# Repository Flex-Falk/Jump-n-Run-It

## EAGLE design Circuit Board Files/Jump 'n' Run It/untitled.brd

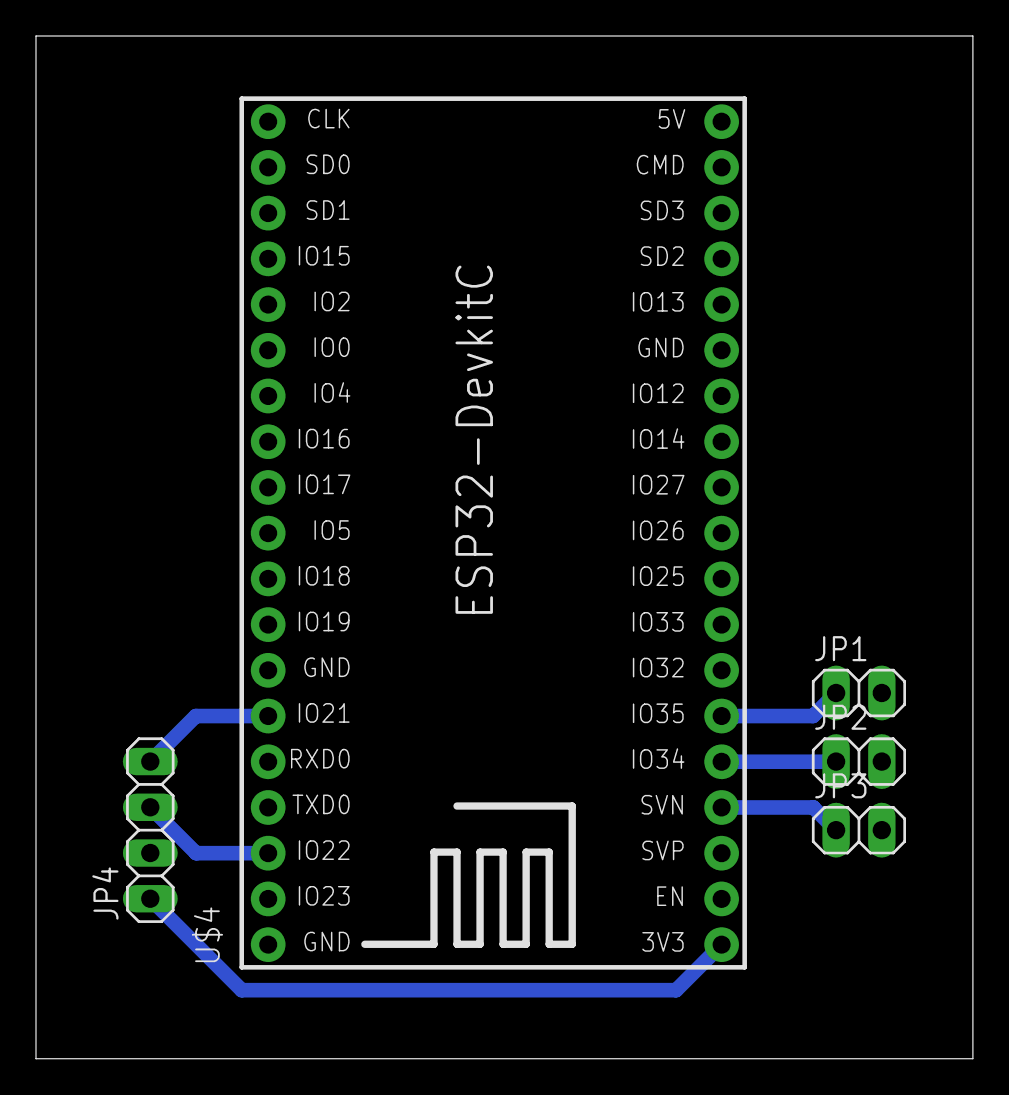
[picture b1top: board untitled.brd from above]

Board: 2 copper layers, 52.0 x 56.8 mm, 5 parts (0 on the bottom side), 7 nets.

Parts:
JP1, JP2, JP3: 1X02
JP4: 1X04
U$4: ESP32DEVKITC; ESP32-DEVKITC

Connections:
GND: JP1.2, JP2.2, JP3.2, JP4.2, U$4.38
unnamed: JP1.1, U$4.6
unnamed: JP2.1, U$4.5
unnamed: JP3.1, U$4.4
unnamed: JP4.1, U$4.1
unnamed: JP4.4, U$4.33
unnamed: JP4.3, U$4.36

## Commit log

2024-04-05 Added Hand-Drawn Sketch
    Variante Matte
2024-04-11 Basic Architecture, Organized Planning stuff
2024-04-11 Correction
2024-04-18 Created Test-Code for the Capacitive Pressure Sensor
2024-04-25 Functioning RunningMat code
2024-04-25 Small Corrections for ESP code
2024-04-26 Added Endless Game Prototype
    Mein bisheriger Fortschritt mit dem Unity Game, habe noch ein paar Fehler aus dem Tutorial fixen können. Hoffe es ist nicht zu groß für GitHub ^^
2024-04-29 Emulate Key input through ESP
2024-04-30 Updated Architecture
2024-05-01 Added Screenshots of Game
2024-05-02 gitignore
2024-05-02 gitIgnore Update
2024-05-02 Input Handler
2024-05-02 Update gitignore
2024-05-02 RunningMat should now correctly identify steps
2024-05-02 Coherent naming convention (instead of "mat" we use "board")
2024-05-02 Improve documentation for the ESP32 code
2024-05-08 Added Prefabs
    Die Straße generiert sich nun zufällig für ein unendliches Level und es gibt einen GameOver Screen wenn der Spieler mit einem Hindernis collided
2024-05-08 Added Screenshots
2024-05-09 Input + Controll Update
    big changes to the way the player is controlled and moving
2024-05-11 Include EventDataHook, UI to set port, baudrate
2024-05-16 Fixed and Tweaked code for the actual running boards
2024-05-20 Added Crouching + Screenshots
    Man kann nun im Game Mode über die Tastatur mit "c" den Player crouchen damit er unter den größeren Barrieren hindurch kann.
2024-05-27 Added Player Asset + Animations
2024-05-28 Circuit Board Files
2024-05-29 GyrosensorCase Model
2024-05-30 Animation base fix: stuff didnt got pushed properly last time
2024-05-31 Fixed Animations for Jumping & Crouching
2024-06-01 add mpu model
2024-06-01 Add server to use Bluetooth with unity via IPCs
    remove gravity from IMU
    TODO: write handle to communicate the server with unity
2024-06-02 Inital Port is set correctly at startup
2024-06-02 Disable controls when Game Over
2024-06-02 Added SFX and music and fixed unnecessary port display
2024-06-02 Quieter music
2024-06-02 JumpInput Fix
2024-06-02 Crouch Fix & Audio Tweak
2024-06-02 Added Grass, Walls and Lighting
2024-06-02 Models of all the Parts
2024-06-03 Added Coins to collect
2024-06-03 Revert "Added Coins to collect"
    This reverts commit 750d32fb50990cda842bd36838d8ff7ba60380a6.
2024-06-03 Added Screenshot
2024-06-03 Added PowerUps
    Can be collected but have no function yet
2024-06-04 Animation Fix
    Wheel did the jump animation while rolling sometimes (probably due to exiting the ground for a short while switching the ground prefab)
2024-06-06 add ESP NOW to send/receive data between ESP32's
2024-06-07 Moved Collectibles
    Now it is easier for the player to reach them
2024-06-07 Implemented Shield Power Up
    Wenn der Player dieses Power Up einsammelt überlebt er es nun genau einmal mit einem Objekt zu kollidieren
2024-06-07 Minor Changes
2024-06-07 Added Text + implemented SpeedPowerUp
    Man bekommt nun angezeigt ob das Schild aktiv ist oder nicht
2024-06-07 add esp now with imu data
2024-06-08 Tile Prefab Fix
2024-06-08 Coin Sound + Initial Attack Config (pretty ugly and player colliders have to be rearranged)
2024-06-08 (missing from last push)
2024-06-08 Finished Airshot
2024-06-10 Added Score Calculation
    The score of the player is shown in the game over screen: Coins + RunningDistance - Time
2024-06-11 Refactoring + Airshot changes
    Airshot hits every object, crates drop loot.
    Missing: proper Airshot animation, Shield Animation, raising the collectables slightly in the prefab
    Bug: Hitting the poweups with airshots sometimes gets stuck and can hit the player
2024-06-12 Effects for Airshot and Shield
2024-06-13 Small changes & IMU display stats
2024-06-13 add imu com esp_now
2024-06-15 Add func to plot data via seaborn and matplotlib
2024-06-16 Basic Save
    no idea what data we actually need, should be easily modifiable
2024-06-17 Map editing
2024-06-18 Edited Save Functions
2024-06-18 export data
2024-06-18 more data
2024-06-18 fix broken data
2024-06-19 something is wrong with the indexing for manuel labeling
2024-06-20 explosion
2024-06-20 Merged ESP32 codes
2024-06-20 Added screenshots of plotted data
2024-06-20 convert files to rows that contains accel and gyro
2024-06-20 relabel data
2024-06-20 plots
2024-06-22 add ipynb RNN
2024-06-22 First draft of the IMU detection model
2024-06-24 added onnx model to unity. Problem: gives wrong predictions
2024-06-25 test diff model configs todo test v3
2024-06-26 UDP unity to python bidirectional communication
    middleware between unity and master? possible?
2024-06-26 unity stuff
2024-06-27 Added All 3D Objects
2024-06-27 add lstm to server
2024-06-27 comments
2024-06-27 Registered new data, removed y-value detection, updated jupyter notebook load and export (from ONNX to pickle & torch), corrected server load, added tags for unity, movement is now classified by NN, 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
2024-06-27 label 10x Jump, Shoot, Crouch data
    looks good, but we may need to talk over it?
2024-06-27 comment line
2024-06-28 add labels for combination dataset
2024-07-02 Added LSTM, changed training code, added mapping from real life gestures to game mechanics
2024-07-02 Cut SpeedUp in half
    In Unity war der Speed Up nicht so krass und jetzt merk ich gar nichts mehr davon, aber ich hoffe es passt jetzt für das Spielen mit den Brettern
2024-07-02 Decreased Obstacles + edited distances
    Auch hier schwierig in meinem Unity Game festzustellen ob das für die Bretter ausreicht, war auch vorher easy spielbar mit Tastatur, müssen wir testen
2024-07-02 relabled merged data set
2024-07-03 merged dataset and small edit to the training process
2024-07-03 Retrained LSTM on updated merged data set
2024-07-03 Updated the LSTM a bit and took an instanced with a minimized loss value)
2024-07-03 Fixed combined inputs and uncontrollable jump heights
2024-07-03 Prevent spamming of airshot
2024-07-04 new NN model and new dataset/loader
2024-07-04 Functioning Jump (Crouch) recognition through thresholds
2024-07-05 balancing
2024-07-09 gradient_based
2024-07-09 last try prediction via gradient and fix thresholds
2024-07-09 Last Changes, Recordings & First Build
2024-07-09 Revert "last try prediction via gradient and fix thresholds"
    This reverts commit 45cc4ecb3d4cc6016af73011e242c1c402b8726f.
2024-07-09 Revert "gradient_based"
    This reverts commit 25296232e9bf7432211559f57bdfad3db7a94ef1.
2024-07-09 Revert "balancing"
    This reverts commit 526cba47bd9abb3f62544e9676a274228026f2d7.
2024-07-09 Fix Double Jump
2024-07-09 Fixed Speedup, Organized Files & Created new Game Build
2024-07-10 Video stuff
2024-07-10 more Videos
2024-07-11 Final Video
